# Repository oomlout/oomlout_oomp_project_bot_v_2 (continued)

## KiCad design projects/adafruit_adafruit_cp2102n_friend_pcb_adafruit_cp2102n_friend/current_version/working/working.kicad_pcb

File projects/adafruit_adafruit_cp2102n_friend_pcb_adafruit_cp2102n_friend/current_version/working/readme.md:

# adafruit_cp2102n_friend_pcb
 
## summary 
* id: adafruit_adafruit_cp2102n_friend_pcb_adafruit_cp2102n_friend
* user: adafruit
* name: adafruit_cp2102n_friend_pcb
* board: adafruit_cp2102n_friend
* repo: https://github.com/adafruit/Adafruit-CP2102N-Friend-PCB

* src_file_repo_sch: 
* src_file_repo_sch_link: https://github.com/adafruit/Adafruit-CP2102N-Friend-PCB/tree/main/
* full details link: https://github.com/oomlout/oomlout_oomp_project_bot_v_2/tree/main/projects/adafruit_adafruit_cp2102n_friend_pcb_adafruit_cp2102n_friend/current_version/working  

## schematic  
  
[schematic (pdf)](working_schematic.pdf) 

## pcb  

[board (pdf)](working.pdf)  

## working_bom
| Id | Designator | Footprint | Quantity | Designation | Supplier and ref |  | None | 
| --- | --- | --- | --- | --- | --- | --- | --- | 
| 1 | X2 | USB_C_CUSB31-CFM2AX-01-X | 1 |  |  |  | [''] | 
| 2 | R6,R2,R1 | 0603-NO | 3 | 20K |  |  | [''] | 
| 3 | R5 | 0603-NO | 1 | 47K |  |  | [''] | 
| 4 | D2 | CHIPLED_0603_NOOUTLINE | 1 | GREEN |  |  | [''] | 
| 5 | C2,C5,C3 | 0805-NO | 3 | 10uF |  |  | [''] | 
| 6 | R4,R3 | 0603-NO | 2 | 5.1K |  |  | [''] | 
| 7 | U$19,U$18 | MOUNTINGHOLE_2.0_PLATED | 2 | MOUNTINGHOLE2.0 |  |  | [''] | 
| 8 | JP1 | 1X06_ROUND_76 | 1 | FTDI |  |  | [''] | 
| 9 | D1 | CHIPLED_0603_NOOUTLINE | 1 | RED |  |  | [''] | 
| 10 | C1,C4 | 0603-NO | 2 | 0.1uF |  |  | [''] | 
| 11 | IC1 | QFN24_4MM_SMSC | 1 | CP2102N-24 |  |  | [''] | 
| 12 | FID2,FID1 | FIDUCIAL_1MM | 2 | FIDUCIAL_1MM |  |  | [''] | 
| 13 | U$8 | ADAFRUIT_2.5MM | 1 |  |  |  | [''] | 
| 14 | JP4 | 1X08_ROUND_70 | 1 | Control |  |  | [''] | 
| 15 | JP2 | 1X08_ROUND_70 | 1 | Modem |  |  | [''] | 
| 16 | U$17 | PCBFEAT-REV-040 | 1 |  |  |  | [''] | 
| 17 | U$22 | ADAFRUIT_5MM | 1 |  |  |  | [''] | 

## bom_schematic
| Ref | Qnty | Value | Cmp name | Footprint | Description | Vendor | DNP | 
| --- | --- | --- | --- | --- | --- | --- | --- | 
| C1, C4 | 2 | 0.1uF | CAP_CERAMIC0603_NO | working:0603-NO |  |  |  | 
| C2, C3, C5 | 3 | 10uF | CAP_CERAMIC0805-NOOUTLINE | working:0805-NO |  |  |  | 
| D1 | 1 | RED | LED0603_NOOUTLINE | working:CHIPLED_0603_NOOUTLINE |  |  |  | 
| D2 | 1 | GREEN | LED0603_NOOUTLINE | working:CHIPLED_0603_NOOUTLINE |  |  |  | 
| FID1, FID2 | 2 | FIDUCIAL_1MM | FIDUCIAL_1MM | working:FIDUCIAL_1MM |  |  |  | 
| IC1 | 1 | CP2102N-24 | CP2102N-24 | working:QFN24_4MM_SMSC |  |  |  | 
| JP1 | 1 | FTDI | HEADER-1X676MIL | working:1X06_ROUND_76 |  |  |  | 
| JP2 | 1 | Modem | HEADER-1X870MIL | working:1X08_ROUND_70 |  |  |  | 
| JP4 | 1 | Control | HEADER-1X870MIL | working:1X08_ROUND_70 |  |  |  | 
| R1, R2, R6 | 3 | 20K | RESISTOR_0603_NOOUT | working:0603-NO |  |  |  | 
| R3, R4 | 2 | 5.1K | RESISTOR_0603_NOOUT | working:0603-NO |  |  |  | 
| R5 | 1 | 47K | RESISTOR_0603_NOOUT | working:0603-NO |  |  |  | 
| U$18, U$19 | 2 | MOUNTINGHOLE2.0 | MOUNTINGHOLE2.0 | working:MOUNTINGHOLE_2.0_PLATED |  |  |  | 
| X2 | 1 | USB_C | USB_C | working:USB_C_CUSB31-CFM2AX-01-X |  |  |  | 

## mounting_holes
| x | y | package | value | ref | size | 
| --- | --- | --- | --- | --- | --- | 
| 13.72 | 0.0 | MOUNTINGHOLE_2.0_PLATED | MOUNTINGHOLE2.0 | U$18 | m3 | 
| 0.0 | 0.0 | MOUNTINGHOLE_2.0_PLATED | MOUNTINGHOLE2.0 | U$19 | m3 |

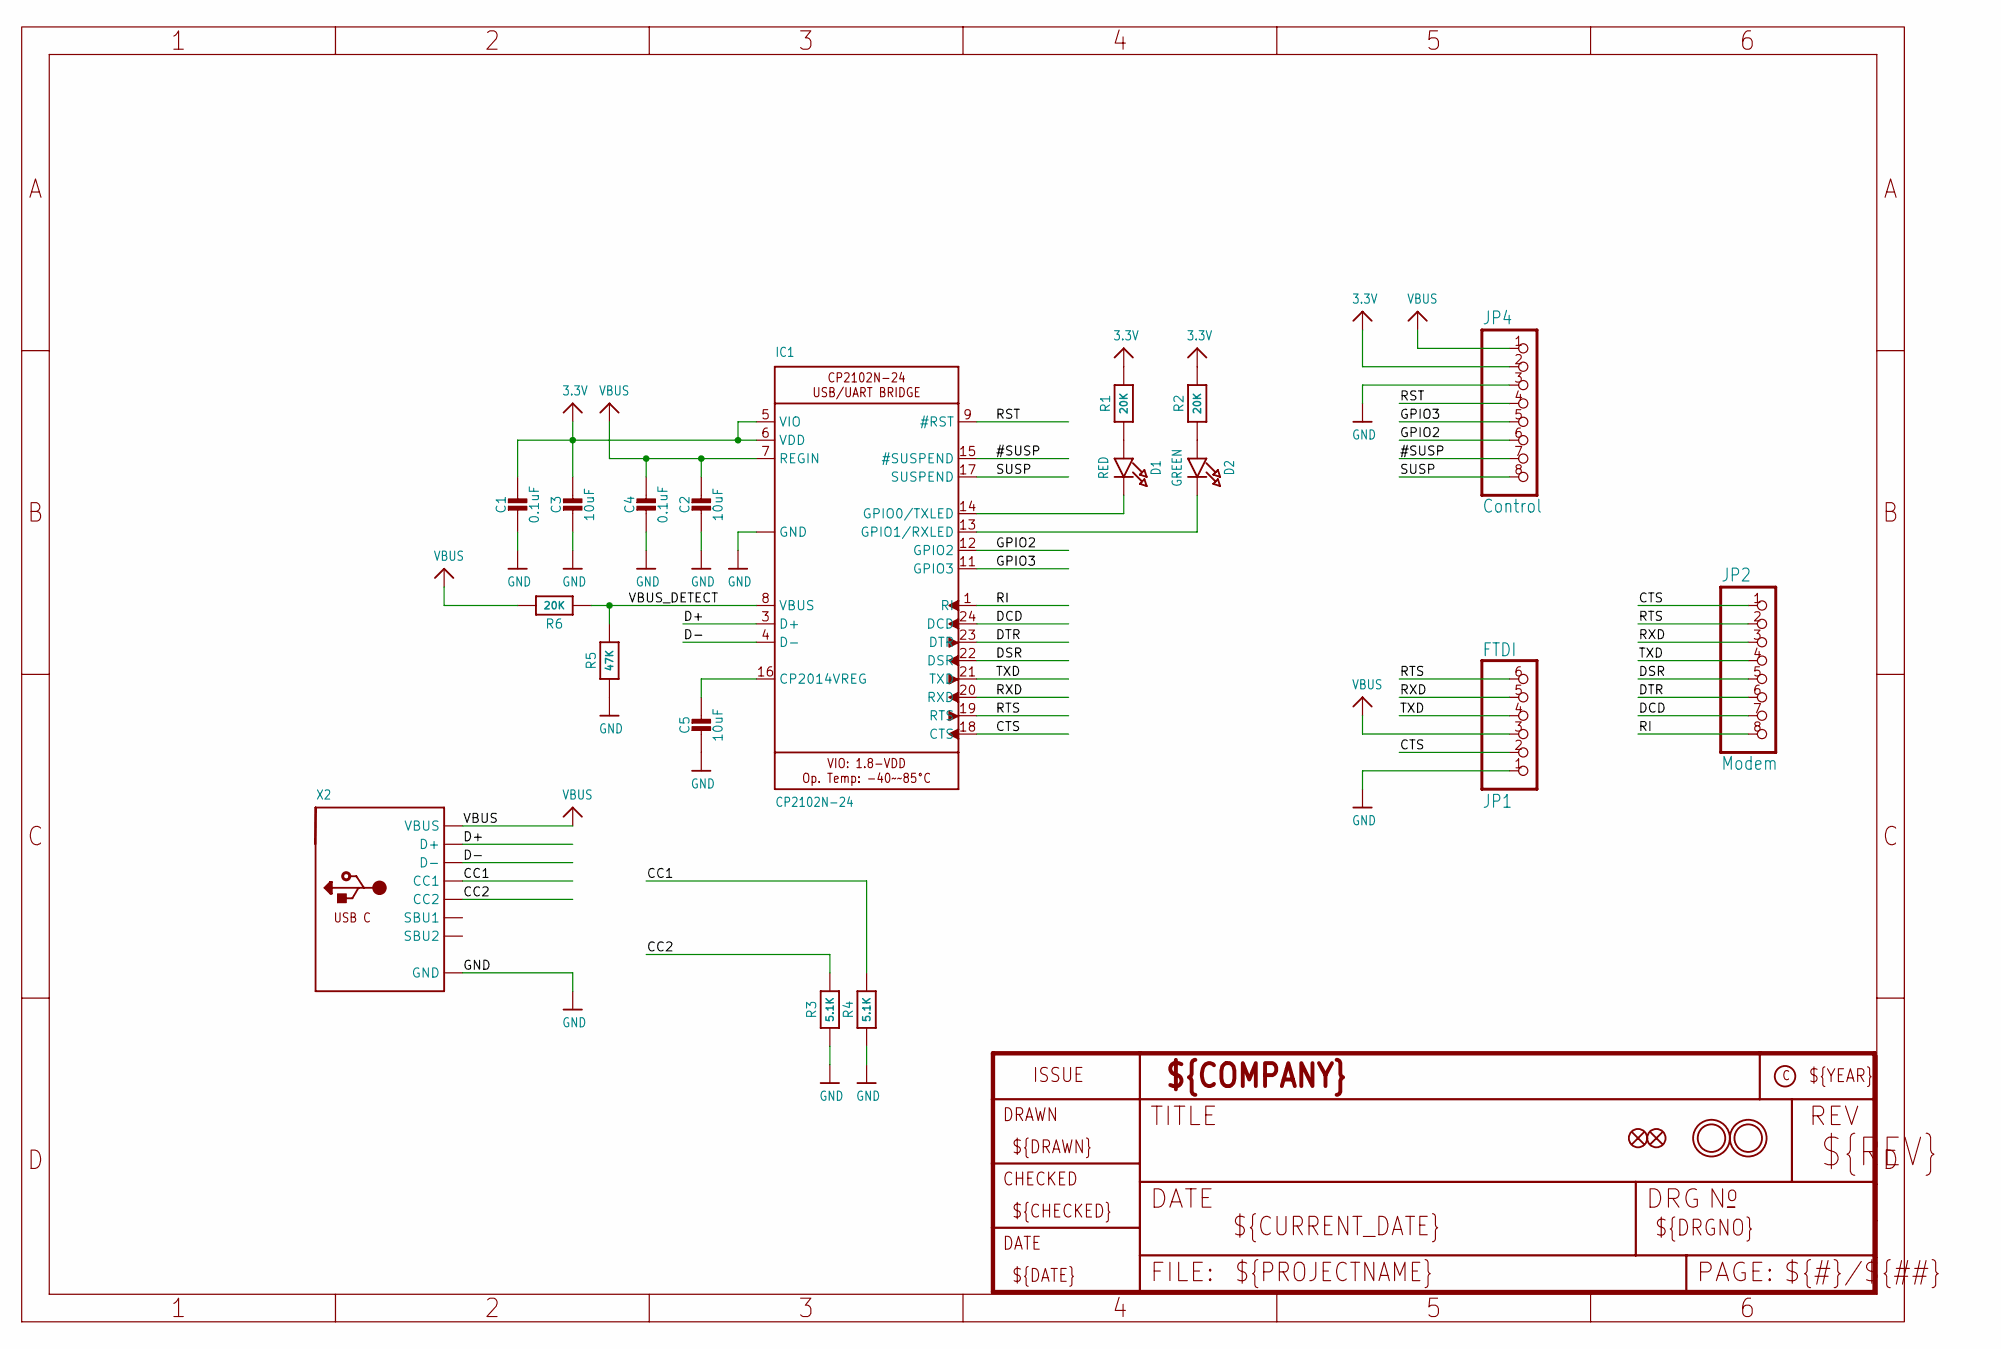
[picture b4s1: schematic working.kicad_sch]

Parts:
C1, C4: 0.1uF; 0603-NO
C2, C3, C5: 10uF; 0805-NO
D1: RED; CHIPLED_0603_NOOUTLINE
D2: GREEN; CHIPLED_0603_NOOUTLINE
FID1, FID2: FIDUCIAL_1MM
IC1: CP2102N-24; QFN24_4MM_SMSC
JP1: FTDI; 1X06_ROUND_76
JP2: Modem; 1X08_ROUND_70
JP4: Control; 1X08_ROUND_70
R1, R2, R6: 20K; 0603-NO
R3, R4: 5.1K; 0603-NO
R5: 47K; 0603-NO
U$18, U$19: MOUNTINGHOLE2.0; MOUNTINGHOLE_2.0_PLATED
X2: USB_C; USB_C_CUSB31-CFM2AX-01-X

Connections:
3.3V: C1.1, C3.1, IC1.5 (VIO), IC1.6 (VDD), JP4.2, R1.2, R2.2
#SUSP: IC1.15 (#SUSPEND), JP4.7
CC1: R4.2, X2.A5 (CC1)
CC2: R3.2, X2.B5 (CC2)
CTS: IC1.18 (CTS), JP1.2, JP2.1
D+: IC1.3 (D+), X2.A6 (D+), X2.B6 (D+)
D-: IC1.4 (D-), X2.A7 (D-), X2.B7 (D-)
DCD: IC1.24 (DCD), JP2.7
DSR: IC1.22 (DSR), JP2.5
DTR: IC1.23 (DTR), JP2.6
GND: C1.2, C2.2, C3.2, C4.2, C5.2, IC1.2 (GND), IC1.THERM (GND), JP1.1, JP4.3, R3.1, R4.1, R5.1, X2.A1B12 (GND), X2.B1A12 (GND)
GPIO2: IC1.12 (GPIO2), JP4.6
GPIO3: IC1.11 (GPIO3), JP4.5
unnamed: D1.A, R1.1
unnamed: C5.1, IC1.16 (CP2014VREG)
unnamed: D2.A, R2.1
unnamed: D1.C, IC1.14 (GPIO0/TXLED)
unnamed: D2.C, IC1.13 (GPIO1/RXLED)
RI: IC1.1 (RI), JP2.8
RST: IC1.9 (#RST), JP4.4
RTS: IC1.19 (RTS), JP1.6, JP2.2
RXD: IC1.20 (RXD), JP1.5, JP2.3
SUSP: IC1.17 (SUSPEND), JP4.8
TXD: IC1.21 (TXD), JP1.4, JP2.4
VBUS: C2.1, C4.1, IC1.7 (REGIN), JP1.3, JP4.1, R6.2, X2.A4B9 (VBUS), X2.B4A9 (VBUS)
VBUS_DETECT: IC1.8 (VBUS), R5.2, R6.1

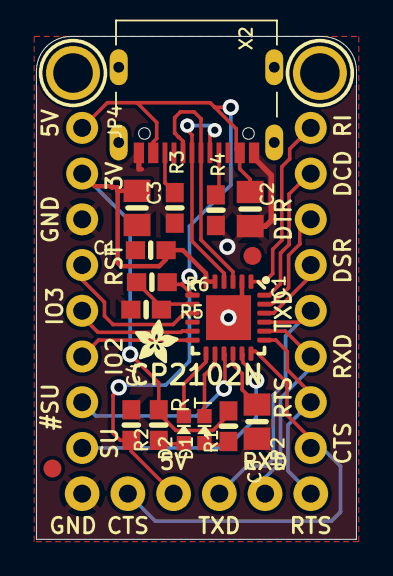
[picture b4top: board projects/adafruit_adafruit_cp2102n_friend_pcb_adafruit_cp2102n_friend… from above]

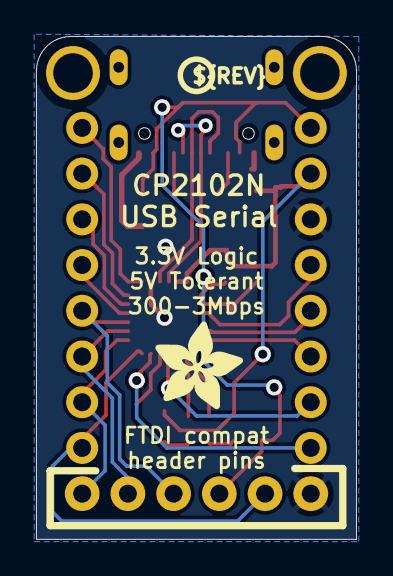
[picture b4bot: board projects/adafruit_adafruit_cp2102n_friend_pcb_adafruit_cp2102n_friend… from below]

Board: 2 copper layers, 17.8 x 27.9 mm, 25 parts (2 on the bottom side), 26 nets.

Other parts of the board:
U$8: ADAFRUIT_2.5MM
U$17: PCBFEAT-REV-040
U$22: ADAFRUIT_5MM

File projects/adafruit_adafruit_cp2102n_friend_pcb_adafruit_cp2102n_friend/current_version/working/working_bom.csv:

"Id";"Designator";"Footprint";"Quantity";"Designation";"Supplier and ref";
1;"X2";"USB_C_CUSB31-CFM2AX-01-X";1;"";;;
2;"R6,R2,R1";"0603-NO";3;"20K";;;
3;"R5";"0603-NO";1;"47K";;;
4;"D2";"CHIPLED_0603_NOOUTLINE";1;"GREEN";;;
5;"C2,C5,C3";"0805-NO";3;"10uF";;;
6;"R4,R3";"0603-NO";2;"5.1K";;;
7;"U$19,U$18";"MOUNTINGHOLE_2.0_PLATED";2;"MOUNTINGHOLE2.0";;;
8;"JP1";"1X06_ROUND_76";1;"FTDI";;;
9;"D1";"CHIPLED_0603_NOOUTLINE";1;"RED";;;
10;"C1,C4";"0603-NO";2;"0.1uF";;;
11;"IC1";"QFN24_4MM_SMSC";1;"CP2102N-24";;;
12;"FID2,FID1";"FIDUCIAL_1MM";2;"FIDUCIAL_1MM";;;
13;"U$8";"ADAFRUIT_2.5MM";1;"";;;
14;"JP4";"1X08_ROUND_70";1;"Control";;;
15;"JP2";"1X08_ROUND_70";1;"Modem";;;
16;"U$17";"PCBFEAT-REV-040";1;"";;;
17;"U$22";"ADAFRUIT_5MM";1;"";;;

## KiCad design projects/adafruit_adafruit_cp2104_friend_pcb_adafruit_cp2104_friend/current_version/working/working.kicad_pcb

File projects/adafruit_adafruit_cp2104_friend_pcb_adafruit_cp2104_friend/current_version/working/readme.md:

# adafruit_cp2104_friend_pcb
 
## summary 
* id: adafruit_adafruit_cp2104_friend_pcb_adafruit_cp2104_friend
* user: adafruit
* name: adafruit_cp2104_friend_pcb
* board: adafruit_cp2104_friend
* repo: https://github.com/adafruit/Adafruit-CP2104-Friend-PCB

* src_file_repo_sch: 
* src_file_repo_sch_link: https://github.com/adafruit/Adafruit-CP2104-Friend-PCB/tree/master/
* full details link: https://github.com/oomlout/oomlout_oomp_project_bot_v_2/tree/main/projects/adafruit_adafruit_cp2104_friend_pcb_adafruit_cp2104_friend/current_version/working  

## schematic  
  
[schematic (pdf)](working_schematic.pdf) 

## pcb  

[board (pdf)](working.pdf)  

## working_bom
| Id | Designator | Footprint | Quantity | Designation | Supplier and ref |  | None | 
| --- | --- | --- | --- | --- | --- | --- | --- | 
| 1 | JP1 | 1X06_ROUND_76 | 1 | FTDI |  |  | [''] | 
| 2 | C2,C3,C1 | 0805-NO | 3 | 10uF |  |  | [''] | 
| 3 | U$8 | ADAFRUIT_2.5MM | 1 |  |  |  | [''] | 
| 4 | FID2,FID1 | FIDUCIAL_1MM | 2 | FIDUCIAL" |  |  | [''] | 
| 5 | U$18,U$19 | MOUNTINGHOLE_2.0_PLATED | 2 | MOUNTINGHOLE2.0 |  |  | [''] | 
| 6 | D1 | CHIPLED_0805_NOOUTLINE | 1 | RED |  |  | [''] | 
| 7 | R1,R2 | 0805-NO | 2 | 1K |  |  | [''] | 
| 8 | C4 | 0805-NO | 1 | 0.1uF |  |  | [''] | 
| 9 | JP2 | 1X08_ROUND_70 | 1 | Modem |  |  | [''] | 
| 10 | JP4 | 1X08_ROUND_70 | 1 | Control |  |  | [''] | 
| 11 | D2 | CHIPLED_0805_NOOUTLINE | 1 | GREEN |  |  | [''] | 
| 12 | U1 | QFN24_4MM_SMSC | 1 | CP2104 |  |  | [''] | 
| 13 | X1 | 4UCONN_20329_V2 | 1 | 20329 |  |  | [''] | 
| 14 | U$22 | ADAFRUIT_5MM | 1 |  |  |  | [''] | 
| 15 | U$17 | PCBFEAT-REV-040 | 1 |  |  |  | [''] | 

## bom_schematic
| Ref | Qnty | Value | Cmp name | Footprint | Description | Vendor | DNP | 
| --- | --- | --- | --- | --- | --- | --- | --- | 
| C1, C2, C3 | 3 | 10uF | CAP_CERAMIC0805-NOOUTLINE | working:0805-NO |  |  |  | 
| C4 | 1 | 0.1uF | CAP_CERAMIC0805-NOOUTLINE | working:0805-NO |  |  |  | 
| D1 | 1 | RED | LED0805_NOOUTLINE | working:CHIPLED_0805_NOOUTLINE |  |  |  | 
| D2 | 1 | GREEN | LED0805_NOOUTLINE | working:CHIPLED_0805_NOOUTLINE |  |  |  | 
| FID1, FID2 | 2 | FIDUCIAL"" | FIDUCIAL{dblquote}{dblquote} | working:FIDUCIAL_1MM |  |  |  | 
| JP1 | 1 | FTDI | HEADER-1X676MIL | working:1X06_ROUND_76 |  |  |  | 
| JP2 | 1 | Modem | HEADER-1X870MIL | working:1X08_ROUND_70 |  |  |  | 
| JP4 | 1 | Control | HEADER-1X870MIL | working:1X08_ROUND_70 |  |  |  | 
| R1, R2 | 2 | 1K | RESISTOR0805_NOOUTLINE | working:0805-NO |  |  |  | 
| U1 | 1 | CP2104 | CP2104 | working:QFN24_4MM_SMSC |  |  |  | 
| U$18, U$19 | 2 | MOUNTINGHOLE2.0 | MOUNTINGHOLE2.0 | working:MOUNTINGHOLE_2.0_PLATED |  |  |  | 
| X1 | 1 | 20329 | USB_MICRO_20329_V2 | working:4UCONN_20329_V2 |  |  |  | 

## mounting_holes
| x | y | package | value | ref | size | 
| --- | --- | --- | --- | --- | --- | 
| 13.72 | 0.0 | MOUNTINGHOLE_2.0_PLATED | MOUNTINGHOLE2.0 | U$18 | m3 | 
| 0.0 | 0.0 | MOUNTINGHOLE_2.0_PLATED | MOUNTINGHOLE2.0 | U$19 | m3 |

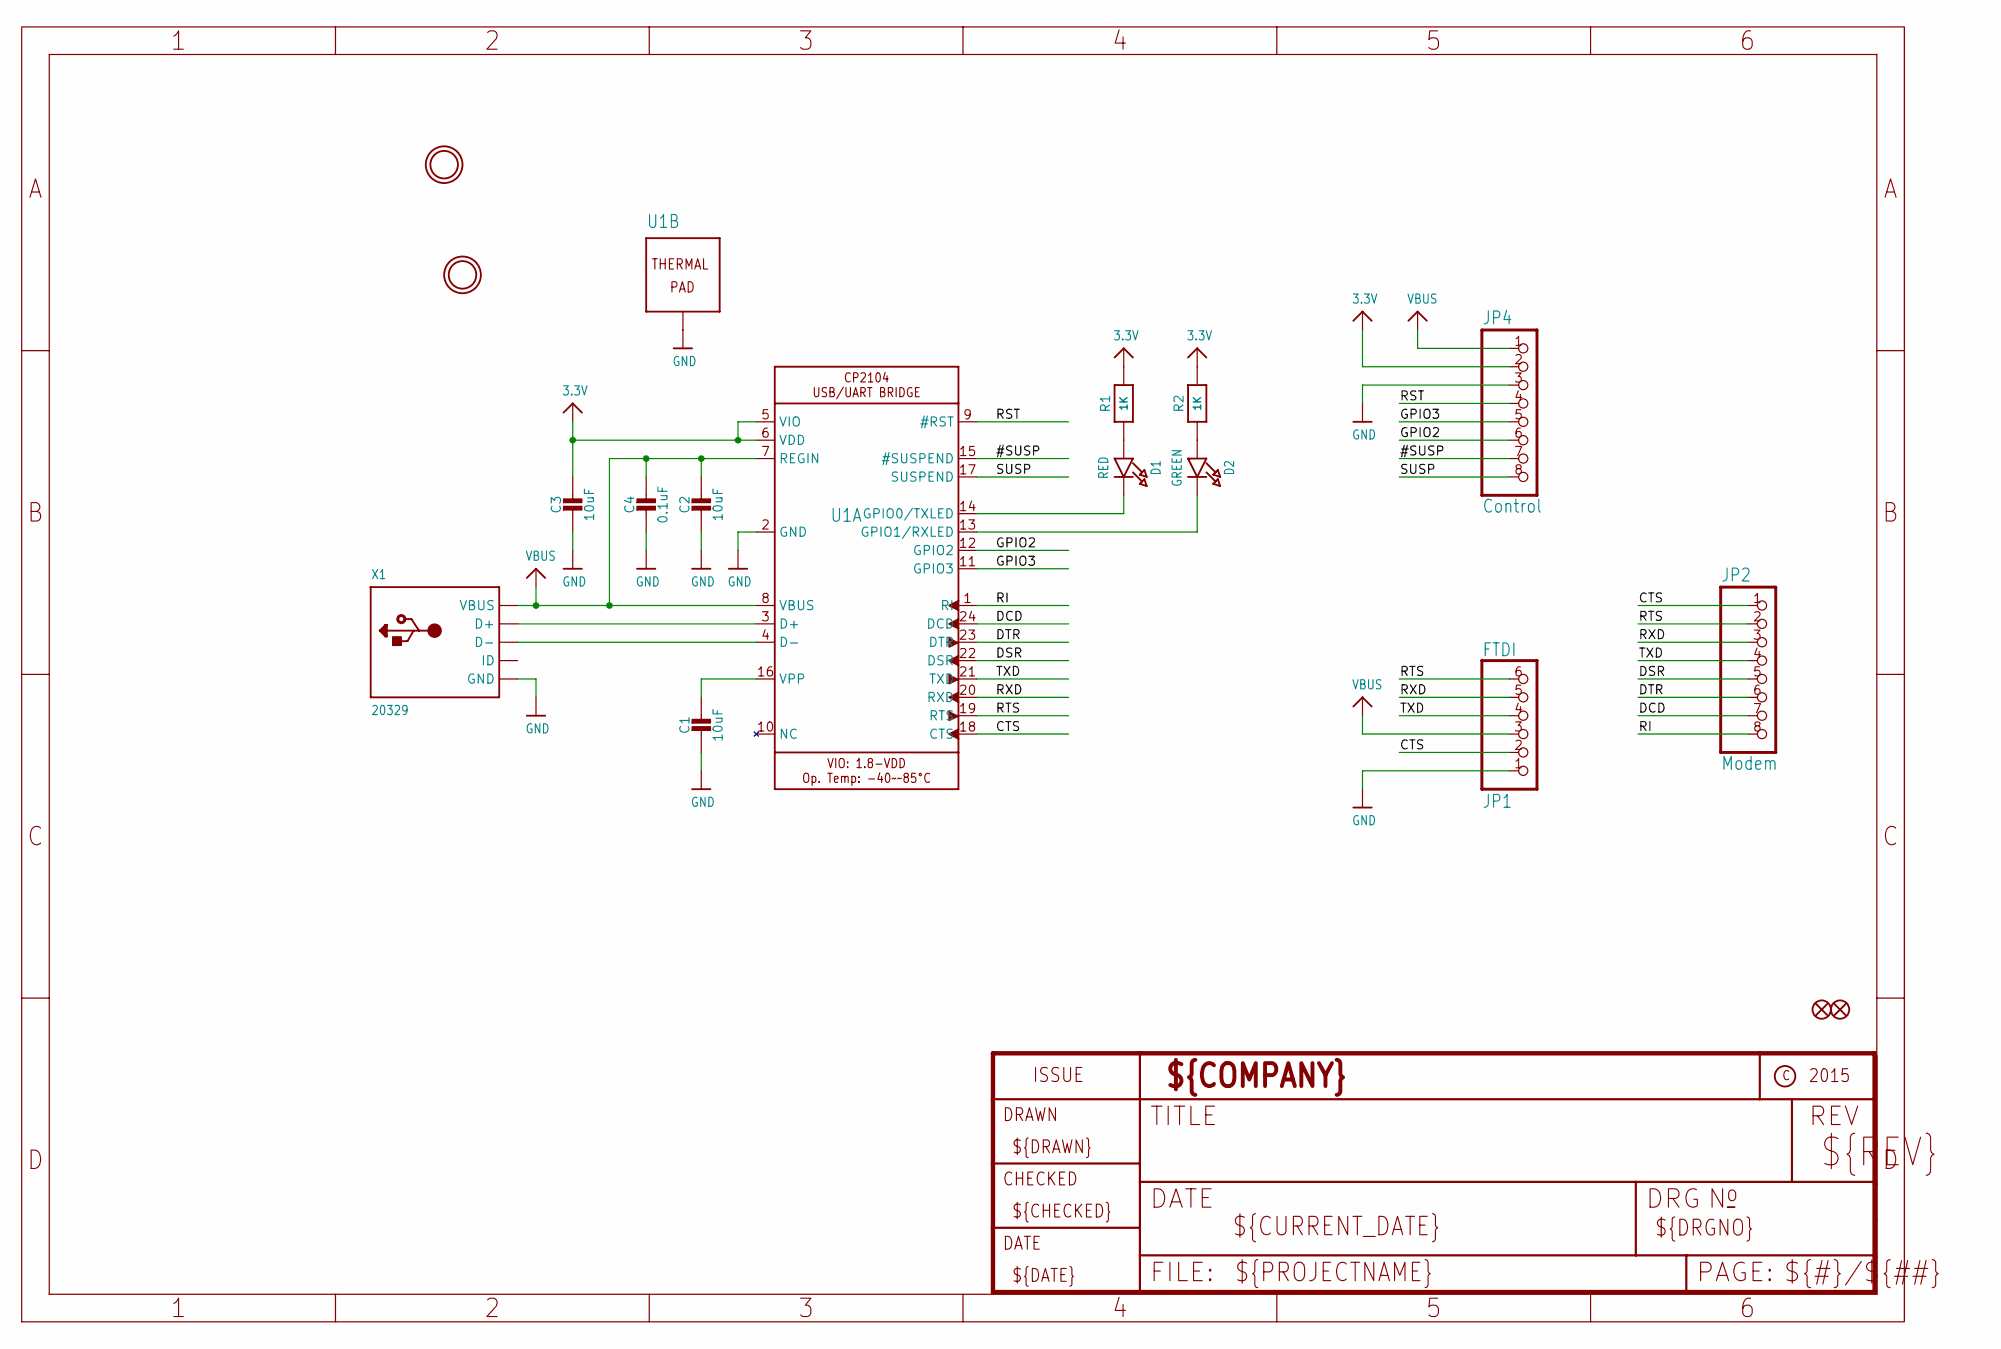
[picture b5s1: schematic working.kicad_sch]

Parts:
C1, C2, C3: 10uF; 0805-NO
C4: 0.1uF; 0805-NO
D1: RED; CHIPLED_0805_NOOUTLINE
D2: GREEN; CHIPLED_0805_NOOUTLINE
FID1, FID2: FIDUCIAL""; FIDUCIAL_1MM
JP1: FTDI; 1X06_ROUND_76
JP2: Modem; 1X08_ROUND_70
JP4: Control; 1X08_ROUND_70
R1, R2: 1K; 0805-NO
U1: CP2104; QFN24_4MM_SMSC
U$18, U$19: MOUNTINGHOLE2.0; MOUNTINGHOLE_2.0_PLATED
X1: 20329; 4UCONN_20329_V2

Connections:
3.3V: C3.1, JP4.2, R1.2, R2.2, U1.5 (VIO), U1.6 (VDD)
#SUSP: JP4.7, U1.15 (#SUSPEND)
CTS: JP1.2, JP2.1, U1.18 (CTS)
DCD: JP2.7, U1.24 (DCD)
DSR: JP2.5, U1.22 (DSR)
DTR: JP2.6, U1.23 (DTR)
GND: C1.2, C2.2, C3.2, C4.2, JP1.1, JP4.3, U1.2 (GND), U1.THERM (TP), X1.BASE@1 (GND), X1.BASE@2 (GND), X1.GND, X1.SPRT@1 (GND), X1.SPRT@2 (GND), X1.SPRT@3 (GND), X1.SPRT@4 (GND)
GPIO2: JP4.6, U1.12 (GPIO2)
GPIO3: JP4.5, U1.11 (GPIO3)
unnamed: D1.A, R1.1
unnamed: U1.3 (D+), X1.D+
unnamed: U1.4 (D-), X1.D-
unnamed: C1.1, U1.16 (VPP)
unnamed: D2.A, R2.1
unnamed: D1.C, U1.14 (GPIO0/TXLED)
unnamed: D2.C, U1.13 (GPIO1/RXLED)
RI: JP2.8, U1.1 (RI)
RST: JP4.4, U1.9 (#RST)
RTS: JP1.6, JP2.2, U1.19 (RTS)
RXD: JP1.5, JP2.3, U1.20 (RXD)
SUSP: JP4.8, U1.17 (SUSPEND)
TXD: JP1.4, JP2.4, U1.21 (TXD)
VBUS: C2.1, C4.1, JP1.3, JP4.1, U1.7 (REGIN), U1.8 (VBUS), X1.VBUS

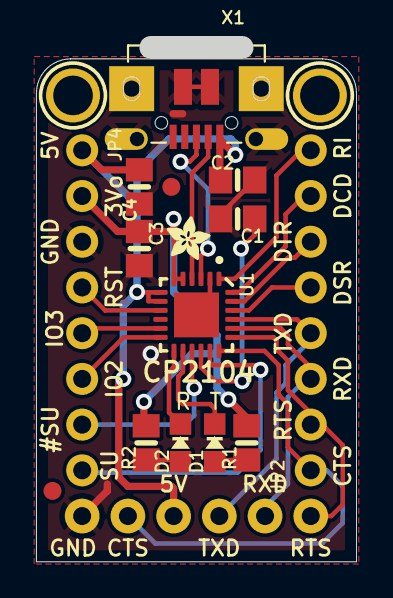
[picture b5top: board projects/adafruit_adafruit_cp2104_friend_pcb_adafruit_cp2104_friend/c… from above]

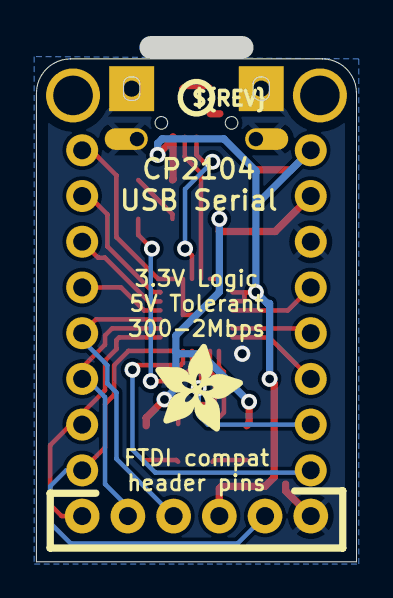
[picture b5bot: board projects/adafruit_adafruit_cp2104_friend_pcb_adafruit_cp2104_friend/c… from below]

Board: 2 copper layers, 17.8 x 28.6 mm, 20 parts (2 on the bottom side), 23 nets.

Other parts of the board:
U$8: ADAFRUIT_2.5MM
U$17: PCBFEAT-REV-040
U$22: ADAFRUIT_5MM

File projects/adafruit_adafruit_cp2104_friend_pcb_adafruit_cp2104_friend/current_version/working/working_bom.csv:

"Id";"Designator";"Footprint";"Quantity";"Designation";"Supplier and ref";
1;"JP1";"1X06_ROUND_76";1;"FTDI";;;
2;"C2,C3,C1";"0805-NO";3;"10uF";;;
3;"U$8";"ADAFRUIT_2.5MM";1;"";;;
4;"FID2,FID1";"FIDUCIAL_1MM";2;"FIDUCIAL""";;;
5;"U$18,U$19";"MOUNTINGHOLE_2.0_PLATED";2;"MOUNTINGHOLE2.0";;;
6;"D1";"CHIPLED_0805_NOOUTLINE";1;"RED";;;
7;"R1,R2";"0805-NO";2;"1K";;;
8;"C4";"0805-NO";1;"0.1uF";;;
9;"JP2";"1X08_ROUND_70";1;"Modem";;;
10;"JP4";"1X08_ROUND_70";1;"Control";;;
11;"D2";"CHIPLED_0805_NOOUTLINE";1;"GREEN";;;
12;"U1";"QFN24_4MM_SMSC";1;"CP2104";;;
13;"X1";"4UCONN_20329_V2";1;"20329";;;
14;"U$22";"ADAFRUIT_5MM";1;"";;;
15;"U$17";"PCBFEAT-REV-040";1;"";;;

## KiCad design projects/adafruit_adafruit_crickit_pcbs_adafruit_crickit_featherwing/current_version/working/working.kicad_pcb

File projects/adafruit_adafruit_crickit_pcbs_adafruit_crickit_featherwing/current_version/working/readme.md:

# adafruit_crickit_pcbs
 
## summary 
* id: adafruit_adafruit_crickit_pcbs_adafruit_crickit_featherwing
* user: adafruit
* name: adafruit_crickit_pcbs
* board: adafruit_crickit_featherwing
* repo: https://github.com/adafruit/Adafruit_Crickit_PCBs

* src_file_repo_sch: 
* src_file_repo_sch_link: https://github.com/adafruit/Adafruit_Crickit_PCBs/tree/master/
* full details link: https://github.com/oomlout/oomlout_oomp_project_bot_v_2/tree/main/projects/adafruit_adafruit_crickit_pcbs_adafruit_crickit_featherwing/current_version/working  

## schematic  
  
[schematic (pdf)](working_schematic.pdf) 

## pcb  

[board (pdf)](working.pdf)  

## working_bom
| Id | Designator | Footprint | Quantity | Designation | Supplier and ref |  | None | 
| --- | --- | --- | --- | --- | --- | --- | --- | 
| 1 | C11,C18,C6,C12,C20,C22 | 0805-NO | 6 | 0.1uF |  |  | [''] | 
| 2 | U$74 | CRICKIT_WING_TOP | 1 |  |  |  | [''] | 
| 3 | JP4 | 1X12_ROUND | 1 |  |  |  | [''] | 
| 4 | C17,C19,C7,C15,C21,C2,C16 | 0805-NO | 7 | 10uF |  |  | [''] | 
| 5 | R17,R8,R11,R16,R1 | 0603-NO | 5 | 264K |  |  | [''] | 
| 6 | L0 | CHIPLED_0805_NOOUTLINE | 1 | yellow |  |  | [''] | 
| 7 | C8 | 0603-NO | 1 | DNP |  |  | [''] | 
| 8 | U$51,U$41,U$43,U$50,U$52,U$42,U$49,U$44 | MOUNTINGHOLE_3.0_NPH | 8 | MOUNTINGHOLE3.0_NPH |  |  | [''] | 
| 9 | TP32,TP29,TP30,TP31 | PCB_ALLI | 4 | SEWTAPPCB_ALLIGATOR |  |  | [''] | 
| 10 | R2,R18,R6,R15,R5,R7 | 0603-NO | 6 | 2.2K |  |  | [''] | 
| 11 | JP2 | TERMBLOC_1X5-3.5MM | 1 | 3.5mm |  |  | [''] | 
| 12 | SPKR0 | TERMBLOCK_1X2-3.5MM | 1 | 3.5mm |  |  | [''] | 
| 13 | R10,R9 | 0603-NO | 2 | 1Mohm |  |  | [''] | 
| 14 | MS2 | FEATHERWING_SMT2 | 1 | FEATHERWING_SMTDUAL |  |  | [''] | 
| 15 | LED1 | LED3535 | 1 | WS2812B3535 |  |  | [''] | 
| 16 | C5 | 0805-NO | 1 | 10ÂµF |  |  | [''] | 
| 17 | JP8 | TERMBLOC_1X5-3.5MM | 1 | 5pin 3.5mm |  |  | [''] | 
| 18 | R4,R3 | _1206 | 2 | 0.2Î© |  |  | [''] | 
| 19 | FID2,FID3,FID1 | FIDUCIAL_1MM | 3 | FIDUCIAL_1MM |  |  | [''] | 
| 20 | U2 | HTSSOP16 | 1 | DRV8833PWPR |  |  | [''] | 
| 21 | GPIO0 | 3X08 | 1 | 3x8 FEMALE |  |  | [''] | 
| 22 | C1,C4 | 0805-NO | 2 | 10ÂµF/16V |  |  | [''] | 
| 23 | C14,C13 | 0805-NO | 2 | 1uF |  |  | [''] | 
| 24 | D1,D2 | SOD-323 | 2 | 1N4148 |  |  | [''] | 
| 25 | C10 | PANASONIC_C | 1 | 47uF+/16v |  |  | [''] | 
| 26 | C3 | 0805_10MGAP | 1 | 1uF |  |  | [''] | 
| 27 | SERVO0 | 3X04 | 1 | 3x4 Male |  |  | [''] | 
| 28 | NEOPIX0 | TERMBLOCK_1X3-3.5MM | 1 | 3.5mm |  |  | [''] | 
| 29 | SJ1 | SOLDERJUMPER_CLOSEDWIRE | 1 |  |  |  | [''] | 
| 30 | SW1 | EVQ-Q2_SMALLER | 1 | EVQQ2 |  |  | [''] | 
| 31 | ON/OFF0 | EG1390 | 1 | MSS-22C01G2 |  |  | [''] | 
| 32 | IC2 | SO16 | 1 | ULN2003AD |  |  | [''] | 
| 33 | R13,R12 | 0805-NO | 2 | 100 |  |  | [''] | 
| 34 | C9 | PANASONIC_C | 1 | 47uF/16v |  |  | [''] | 
| 35 | VR2 | TRIMPOT_BOURNS_3303W | 1 | 10K trim |  |  | [''] | 
| 36 | JP5 | 1X01_ROUND | 1 |  |  |  | [''] | 
| 37 | FB1 | 0805-NO | 1 | Ferrite |  |  | [''] | 
| 38 | U5 | MSOP8_0.65MM | 1 | PAM8302AASCR |  |  | [''] | 
| 39 | POWERFAIL0 | CHIPLED_0805_NOOUTLINE | 1 | red |  |  | [''] | 
| 40 | JP1 | 1X02_ROUND | 1 |  |  |  | [''] | 
| 41 | R14 | 0603-NO | 1 | 510 |  |  | [''] | 
| 42 | CN1 | 4UCONN_20329_V2 | 1 | 4U#20329 |  |  | [''] | 
| 43 | U1 | SOT23-5 | 1 | mic5225-3.3 |  |  | [''] | 
| 44 | JP3 | 1X16_ROUND | 1 |  |  |  | [''] | 
| 45 | IC4 | WSON8 | 1 | TPS259573 |  |  | [''] | 
| 46 | Q2 | POWERDI3333 | 1 | AON7401 |  |  | [''] | 
| 47 | X2 | DCJACK_2MM_PTH | 1 | 2.1mm DC |  |  | [''] | 
| 48 | IC3 | SOT23-5 | 1 | 74AHCT1G125DBV |  |  | [''] | 
| 49 | POWEROK0 | CHIPLED_0805_NOOUTLINE | 1 | green |  |  | [''] | 
| 50 | U$4 | TQFN48_7MM | 1 | ATSAMD21G_QFN |  |  | [''] | 
| 51 | SJ7 | SOLDERJUMPER_ARROW_NOPASTE | 1 | ISENSEA |  |  | [''] | 
| 52 | TP1,TP2,TP3 | TP15R | 3 | TPTP15R |  |  | [''] | 
| 53 | U$76 | PCBFEAT-REV-040 | 1 |  |  |  | [''] | 
| 54 | SJ8 | SOLDERJUMPER_ARROW_NOPASTE | 1 | ISENSEB |  |  | [''] | 
| 55 | U$72 | CRICKIT_WING_BOT | 1 |  |  |  | [''] | 

## bom_schematic
no data

## mounting_holes
| x | y | package | value | ref | size | 
| --- | --- | --- | --- | --- | --- | 
| 21.59 | 0.0 | MOUNTINGHOLE_3.0_NPH | MOUNTINGHOLE3.0_NPH | U$41 | m3 | 
| 53.85 | 0.0 | MOUNTINGHOLE_3.0_NPH | MOUNTINGHOLE3.0_NPH | U$42 | m3 | 
| 0.0 | 21.59 | MOUNTINGHOLE_3.0_NPH | MOUNTINGHOLE3.0_NPH | U$43 | m3 | 
| 75.44 | 21.59 | MOUNTINGHOLE_3.0_NPH | MOUNTINGHOLE3.0_NPH | U$44 | m3 | 
| 75.44 | 53.85 | MOUNTINGHOLE_3.0_NPH | MOUNTINGHOLE3.0_NPH | U$49 | m3 | 
| 0.0 | 53.85 | MOUNTINGHOLE_3.0_NPH | MOUNTINGHOLE3.0_NPH | U$50 | m3 | 
| 21.59 | 75.44 | MOUNTINGHOLE_3.0_NPH | MOUNTINGHOLE3.0_NPH | U$51 | m3 | 
| 53.85 | 75.44 | MOUNTINGHOLE_3.0_NPH | MOUNTINGHOLE3.0_NPH | U$52 | m3 |

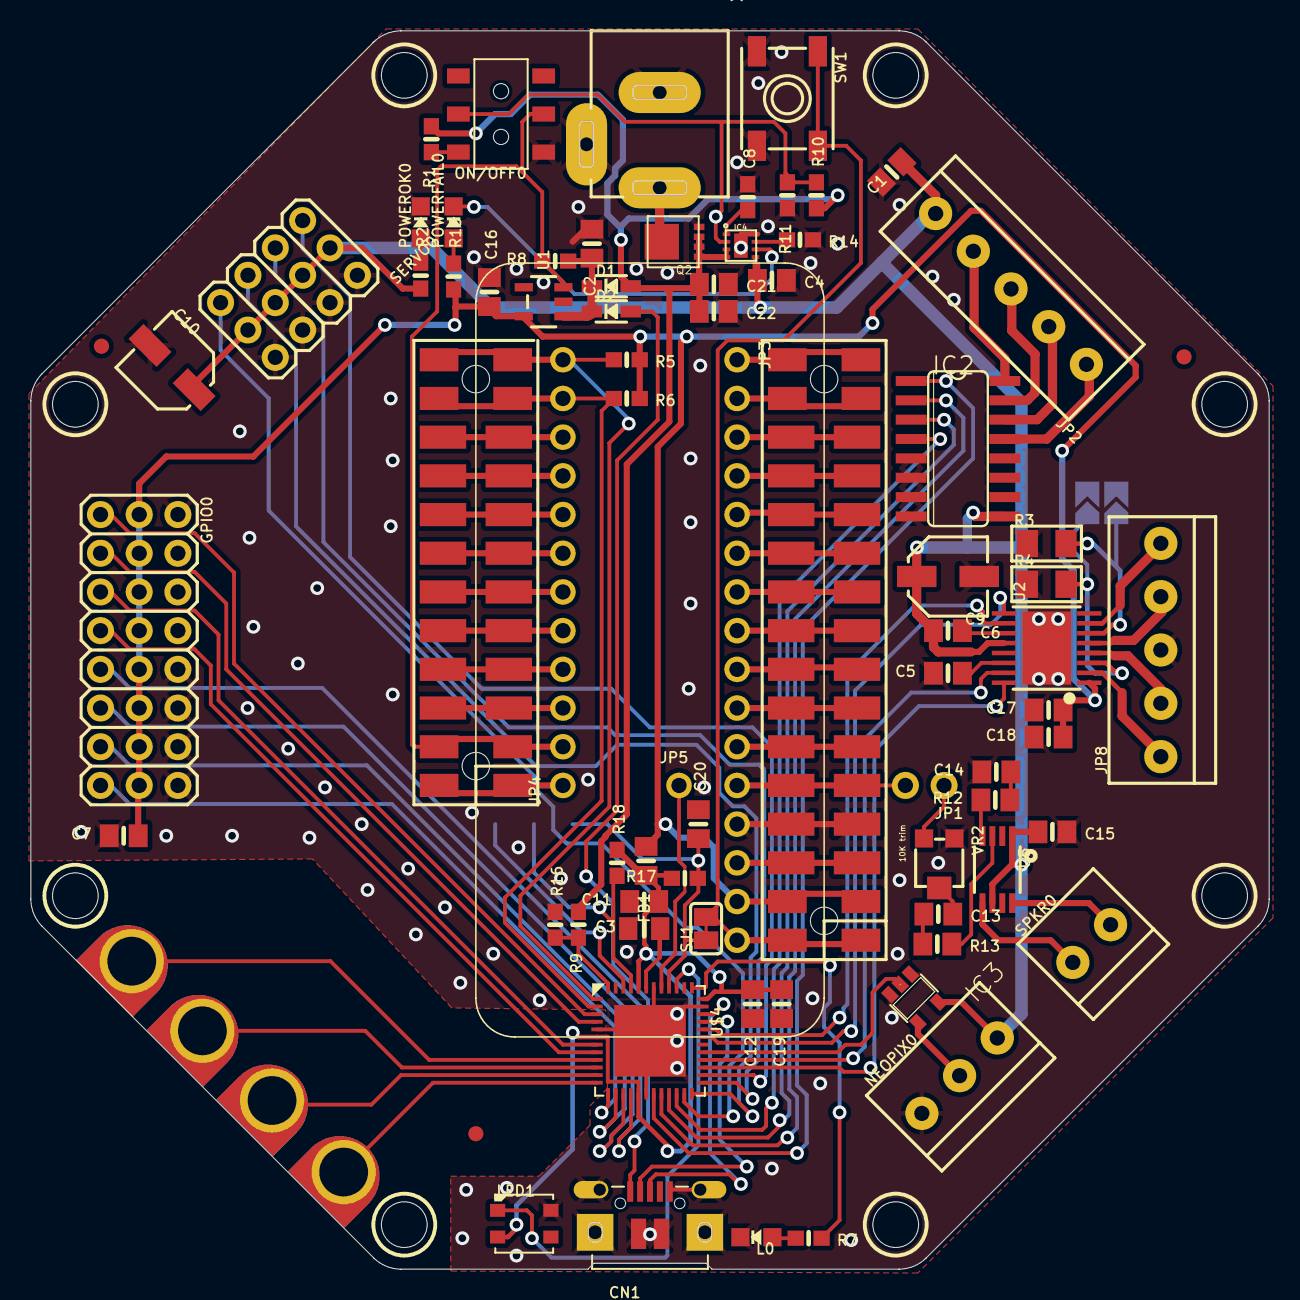
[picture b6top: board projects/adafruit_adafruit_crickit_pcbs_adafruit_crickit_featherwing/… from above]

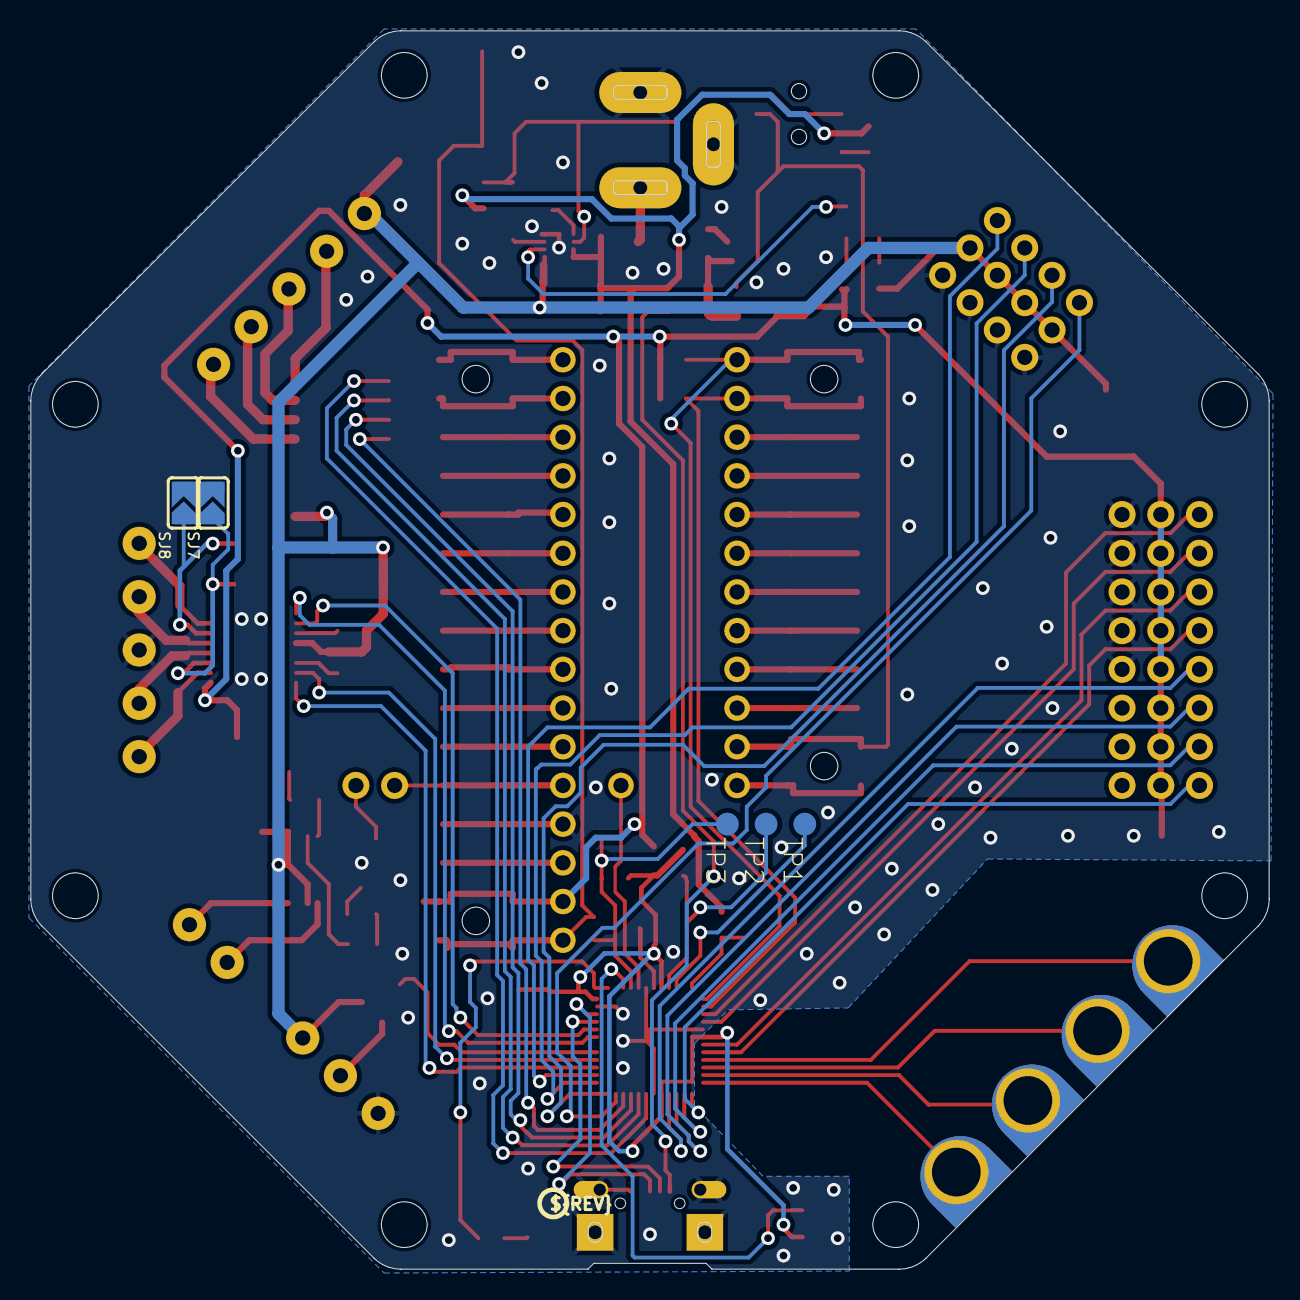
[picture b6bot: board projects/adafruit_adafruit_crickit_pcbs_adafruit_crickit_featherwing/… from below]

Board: 16 copper layers, 81.3 x 81.3 mm, 95 parts (7 on the bottom side), 98 nets.

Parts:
C1, C4: 10µF/16V; 0805-NO
C2, C7, C15, C16, C17, C19, C21: 10uF; 0805-NO
C3: 1uF; 0805_10MGAP
C5: 10µF; 0805-NO
C6, C11, C12, C18, C20, C22: 0.1uF; 0805-NO
C8: DNP; 0603-NO
C9: 47uF/16v; PANASONIC_C
C10: 47uF+/16v; PANASONIC_C
C13, C14: 1uF; 0805-NO
CN1: 4U#20329; 4UCONN_20329_V2
D1, D2: 1N4148; SOD-323
FB1: Ferrite; 0805-NO
FID1, FID2, FID3: FIDUCIAL_1MM
GPIO0: 3x8 FEMALE; 3X08
IC2: ULN2003AD; SO16
IC3: 74AHCT1G125DBV; SOT23-5
IC4: TPS259573; WSON8
JP1: 1X02_ROUND
JP2: 3.5mm; TERMBLOC_1X5-3.5MM
JP3: 1X16_ROUND
JP4: 1X12_ROUND
JP5: 1X01_ROUND
JP8: 5pin 3.5mm; TERMBLOC_1X5-3.5MM
L0: yellow; CHIPLED_0805_NOOUTLINE
LED1: WS2812B3535; LED3535
MS2: FEATHERWING_SMTDUAL; FEATHERWING_SMT2
NEOPIX0: 3.5mm; TERMBLOCK_1X3-3.5MM
ON/OFF0: MSS-22C01G2; EG1390
POWERFAIL0: red; CHIPLED_0805_NOOUTLINE
POWEROK0: green; CHIPLED_0805_NOOUTLINE
Q2: AON7401; POWERDI3333
R1, R8, R11, R16, R17: 264K; 0603-NO
R2, R5, R6, R7, R15, R18: 2.2K; 0603-NO
R3, R4: 0.2Ω; _1206
R9, R10: 1Mohm; 0603-NO
R12, R13: 100; 0805-NO
R14: 510; 0603-NO
SERVO0: 3x4 Male; 3X04
SJ1: SOLDERJUMPER_CLOSEDWIRE
SJ7: ISENSEA; SOLDERJUMPER_ARROW_NOPASTE
SJ8: ISENSEB; SOLDERJUMPER_ARROW_NOPASTE
SPKR0: 3.5mm; TERMBLOCK_1X2-3.5MM
SW1: EVQQ2; EVQ-Q2_SMALLER
TP1, TP2, TP3: TPTP15R; TP15R
TP29, TP30, TP31, TP32: SEWTAPPCB_ALLIGATOR; PCB_ALLI
U1: mic5225-3.3; SOT23-5
U2: DRV8833PWPR; HTSSOP16
U5: PAM8302AASCR; MSOP8_0.65MM
U$4: ATSAMD21G_QFN; TQFN48_7MM
U$41, U$42, U$43, U$44, U$49, U$50, U$51, U$52: MOUNTINGHOLE3.0_NPH; MOUNTINGHOLE_3.0_NPH
U$72: CRICKIT_WING_BOT
U$74: CRICKIT_WING_TOP
U$76: PCBFEAT-REV-040
VR2: 10K trim; TRIMPOT_BOURNS_3303W
X2: 2.1mm DC; DCJACK_2MM_PTH

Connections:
3.3V: C7.1, C16.1, C17.1, C18.1, FB1.1, GPIO0.2, GPIO0.5, GPIO0.8, GPIO0.11, GPIO0.14, GPIO0.17, GPIO0.20, GPIO0.23, JP3.15, MS2.2, MS2.2', R5.2, R6.2, R15.1, U1.5, U2.1
5.0V: C1.1, C4.1, C6.1, C9.+, C10.+, C15.1, IC2.9, IC3.5, IC4.5, JP2.P5, NEOPIX0.1, R2.1, SERVO0.2, SERVO0.5, SERVO0.8, SERVO0.11, U2.12, U5.1, U5.6
ANALOG1: GPIO0.1, U$4.3
ANALOG2: GPIO0.4, U$4.4
ANALOG3: GPIO0.7, U$4.7
ANALOG4: GPIO0.10, U$4.8
ANALOG5: GPIO0.13, U$4.16
ANALOG6: GPIO0.16, U$4.15
ANALOG7: GPIO0.19, U$4.14
ANALOG8: GPIO0.22, U$4.13
AOUT3: JP8.P1, U2.2
AOUT4: JP8.P2, U2.4
AREF: JP3.14, MS2.3, MS2.3'
AUDIO: JP1.1, VR2.3
AUDIO_OUT: JP1.2, JP3.12, MS2.5, MS2.5'
B: JP3.11, MS2.6, MS2.6'
C: JP3.10, MS2.7, MS2.7'
CAPTOUCH1: TP30.P$1, U$4.9
CAPTOUCH2: TP32.P$1, U$4.10
CAPTOUCH3: TP29.P$1, U$4.11
CAPTOUCH4: TP31.P$1, U$4.12
D: JP3.9, MS2.8, MS2.8'
D+: CN1.D+, U$4.34
D-: CN1.D-, U$4.33
DRIVEIN1: IC2.1, U$4.19
DRIVEIN2: IC2.2, U$4.20
DRIVEIN3: IC2.3, U$4.21
DRIVEIN4: IC2.4, U$4.22
DRIVEOUT1: IC2.16, JP2.P4
DRIVEOUT2: IC2.15, JP2.P3
DRIVEOUT3: IC2.14, JP2.P2
DRIVEOUT4: IC2.13, JP2.P1
E: JP3.8, MS2.9, MS2.9'
ENABLE: JP4.2, MS2.27, MS2.27', ON/OFF0.P2, R8.2, U1.3
F: JP3.7, MS2.10, MS2.10'
G: JP3.1, MS2.16, MS2.16'
GND: C1.2, C2.1, C3.2, C4.2, C5.2, C7.2, C8.2, C9.-, C10.-, C11.2, C12.2, C14.2, C15.2, C16.2, C17.2, C18.2, C19.2, C20.2, C21.2, C22.2, CN1.BASE@1, CN1.BASE@2, CN1.GND, CN1.SPRT@1, CN1.SPRT@2, CN1.SPRT@3, CN1.SPRT@4, GPIO0.3, GPIO0.6, GPIO0.9, GPIO0.12, GPIO0.15, GPIO0.18, GPIO0.21, GPIO0.24, IC2.5, IC2.6, IC2.7, IC2.8, IC3.1, IC3.3, IC4.8, IC4.PAD, JP3.13, JP8.P3, L0.C, LED1.4, MS2.4, MS2.4', NEOPIX0.3, ON/OFF0.O2, POWEROK0.C, Q2.4, R3.1, R4.1, R11.2, R14.2, R16.2, SERVO0.3, SERVO0.6, SERVO0.9, SERVO0.12, SJ7.2, SJ8.2, SW1.A, SW1.A', U1.2, U2.13, U2.PPAD, U5.7, U$4.5, U$4.18, U$4.35, U$4.42, U$4.THERMAL, VR2.1, X2.GND, X2.GNDBREAK
INT_NEO: LED1.1, U$4.39
IRQ: JP5.1, U$4.41
L: JP4.6, MS2.23, MS2.23'
LED: R7.2, U$4.37
M: JP4.5, MS2.24, MS2.24'
M1_ASEN: R4.2, SJ7.1, U2.3
M1_BSEN: R3.2, SJ8.1, U2.6
M1_VINT: C5.1, U2.14
MISO: JP3.4, MS2.13, MS2.13'
MOSI: JP3.5, MS2.12, MS2.12'
MOTOR_AIN1: U2.16, U$4.27
MOTOR_AIN2: U2.15, U$4.28
MOTOR_BIN1: U2.9, U$4.31
MOTOR_BIN2: U2.10, U$4.32
N: JP4.4, MS2.25, MS2.25'
unnamed: C6.2, U2.11
unnamed: C2.2, D1.C, D2.C, R8.1, U1.1
unnamed: IC3.4, NEOPIX0.2
unnamed: ON/OFF0.O1, R1.2
unnamed: L0.A, R7.1
unnamed: JP4.7, MS2.22, MS2.22'
unnamed: JP4.8, MS2.21, MS2.21'
unnamed: IC4.7, R14.1
unnamed: JP4.9, MS2.20, MS2.20'
unnamed: JP4.10, MS2.19, MS2.19'
unnamed: POWERFAIL0.A, R15.2
unnamed: IC4.6, POWERFAIL0.C
unnamed: C8.1, IC4.1
unnamed: JP8.P5, U2.7
unnamed: POWEROK0.A, R2.2
unnamed: JP8.P4, U2.5
unnamed: R12.2, U5.4
unnamed: R13.2, U5.3
unnamed: C14.1, R12.1
unnamed: C13.1, R13.1
unnamed: C13.2, VR2.2
NEOPIXEL: IC3.2, U$4.29
PWR: Q2.5678, X2.PWR
RX: JP3.3, MS2.14, MS2.14'
SCL: JP4.11, MS2.18, MS2.18', R6.1, U$4.2
SCLK: JP3.6, MS2.11, MS2.11'
SDA: JP4.12, MS2.17, MS2.17', R5.1, U$4.1
SEESAW_RESET: C20.1, R17.1, SJ1.1, TP3.TP, U$4.40
SERVO1: SERVO0.1, U$4.26
SERVO2: SERVO0.4, U$4.25
SERVO3: SERVO0.7, U$4.24
SERVO4: SERVO0.10, U$4.23
SPKR+: SPKR0.2, U5.5
SPKR-: SPKR0.1, U5.8
SWCLK: R18.1, TP2.TP, U$4.45
SWDIO: TP1.TP, U$4.46
TX: JP3.2, MS2.15, MS2.15'
USB: JP4.3, MS2.26, MS2.26'
VBAT: JP4.1, MS2.28, MS2.28'
VBUS: CN1.VBUS, D2.A
VDD: C11.1, C12.1, C19.1, FB1.2, LED1.2, R17.2, R18.2, U$4.6, U$4.17, U$4.36, U$4.44
VDDCORE: C3.1, U$4.43
VIN: C21.1, C22.1, D1.A, IC4.3, IC4.4, Q2.1, Q2.2, Q2.3, R1.1, R9.1, R10.1
VIN_SENSE: R9.2, R16.1, U$4.48
~RESET: JP3.16, MS2.1, MS2.1', SJ1.2, SW1.B, SW1.B'
~TPSEN: IC4.2, ON/OFF0.P1, R10.2, R11.1
